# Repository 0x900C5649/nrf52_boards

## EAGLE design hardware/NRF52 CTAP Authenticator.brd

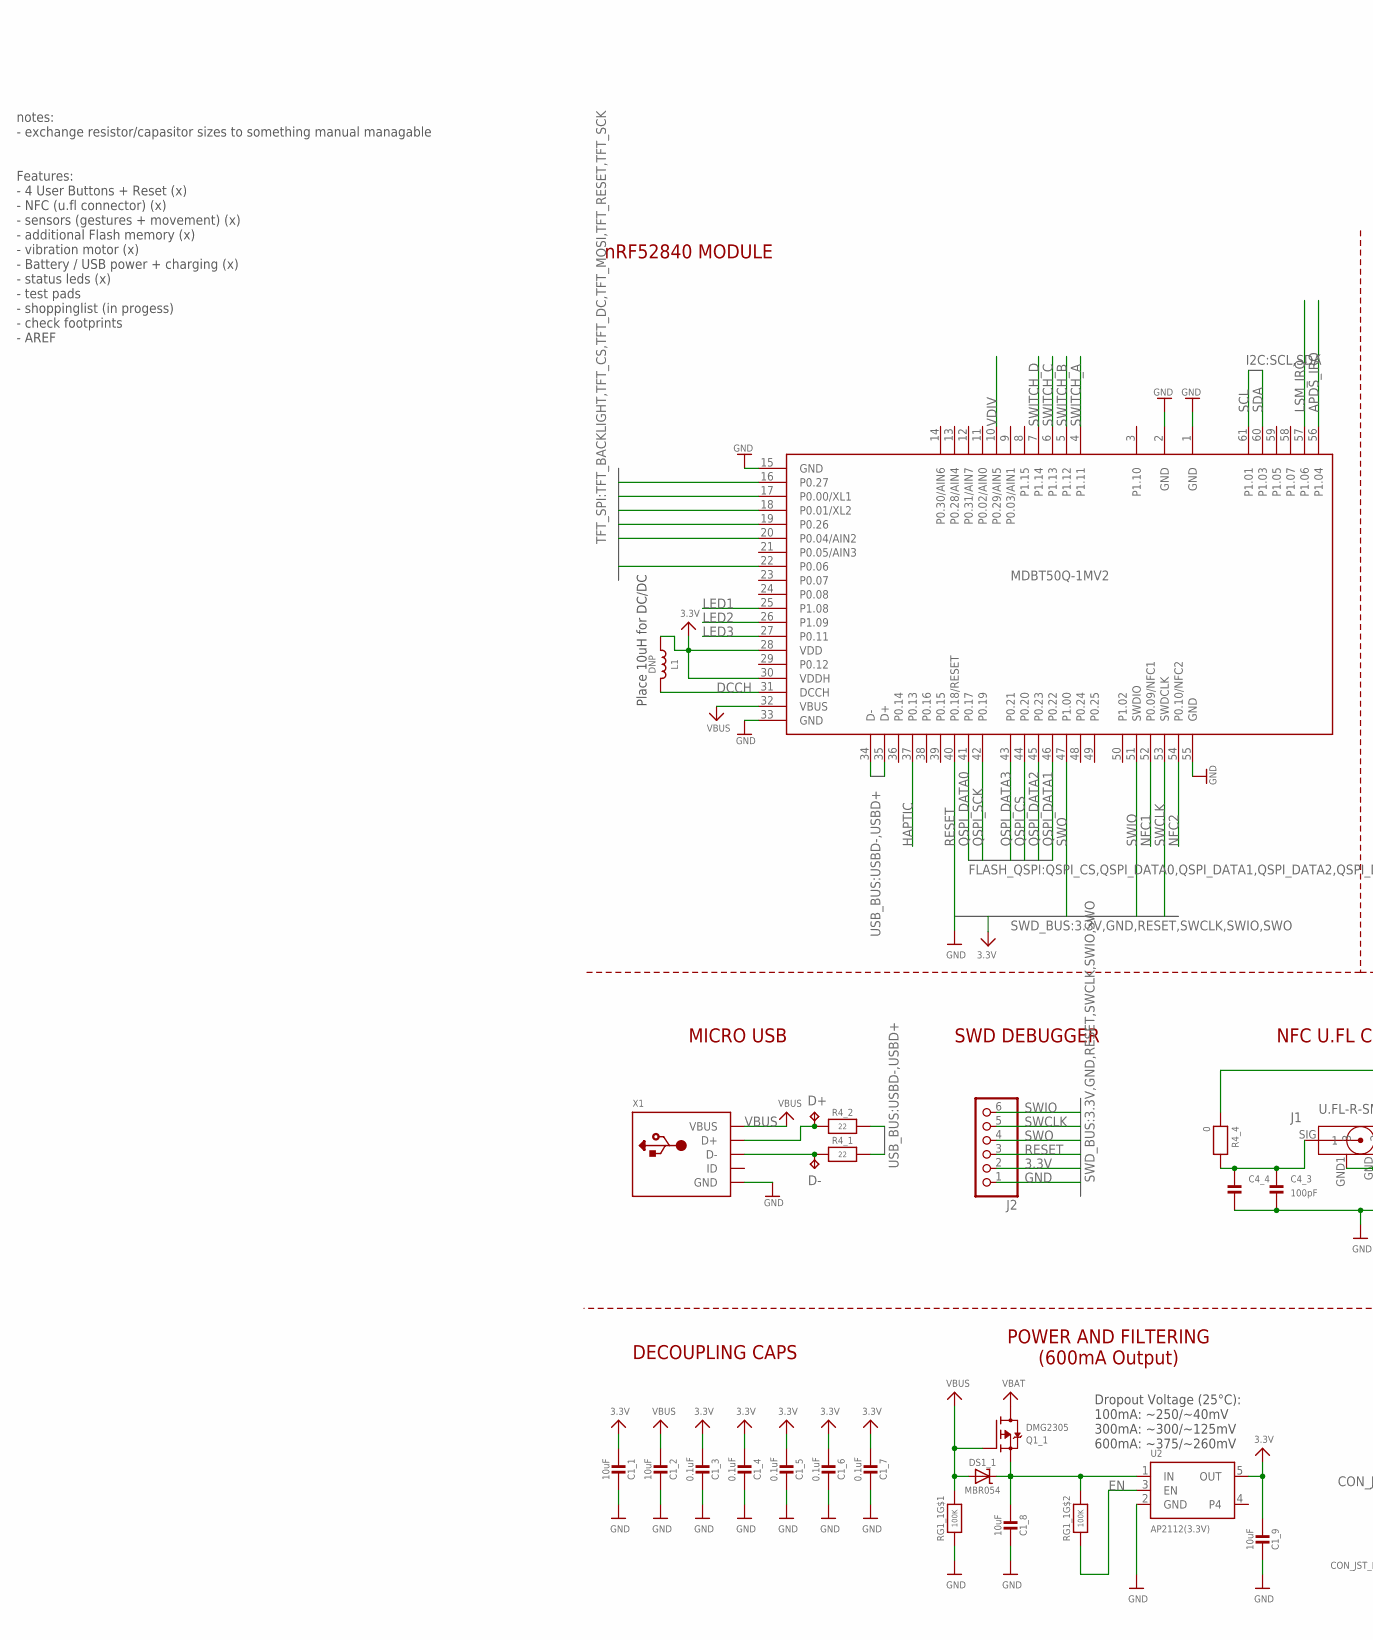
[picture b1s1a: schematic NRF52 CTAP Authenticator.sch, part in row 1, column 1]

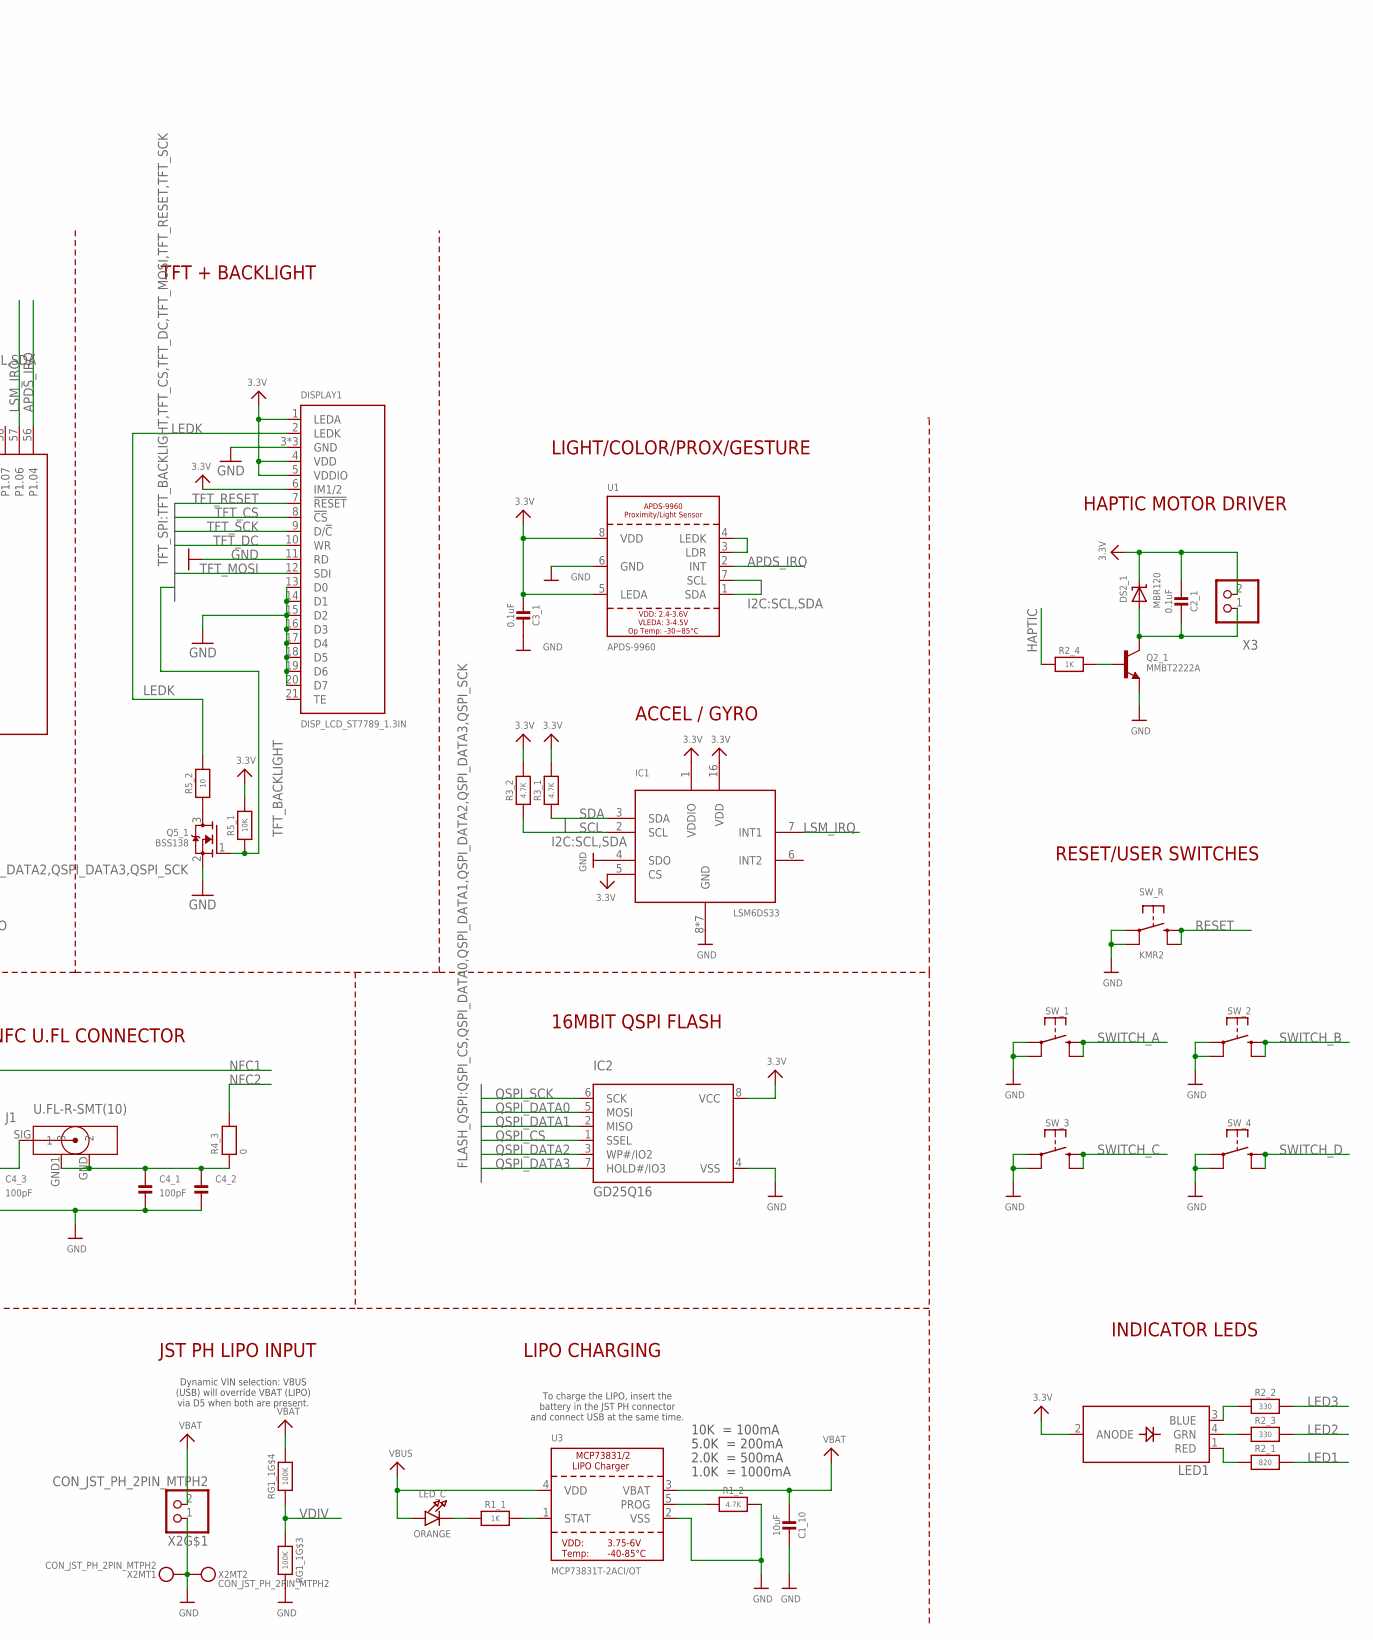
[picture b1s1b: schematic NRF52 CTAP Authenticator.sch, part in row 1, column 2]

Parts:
C1_1, C1_2, C1_8, C1_9, C1_10: 10uF; 0805_NOTHERMALS
C1_3, C1_4, C1_5, C1_6, C1_7, C2_1, C3_1: 0.1uF; 0805_NOTHERMALS
C4_1, C4_3: 100pF; 0805_NOTHERMALS
C4_2, C4_4: CAP_CERAMIC0805-NOTHERMALS; 0805_NOTHERMALS
D+: TPTP10R; TP10R
D-: TPTP10R; TP10R
DISPLAY1: DISP_LCD_ST7789_1.3IN; TFT_1.3IN_240X240_24P
DS1_1: MBR054; SOD-123
DS2_1: MBR120; SOD-123
IC1: LSM6DS33; LGA16_3X3MM
IC2: GD25Q16; SOIC8_150MIL
J1: U.FL-R-SMT(10)
J2: HEADER-1X6ROUND; 1X06_ROUND
L1: DNP; _0805MP
LED1: LED_RGB_PLCC4; RGBLED_PLCC4
LED_C: ORANGE; CHIPLED_0805_NOOUTLINE
MDBT50Q-1MV2: MDBT50
Q1_1: DMG2305; SOT23-R@1
Q2_1: MMBT2222A; SOT23-R
Q5_1: BSS138; SOT23-WIDE
R1_1, R2_4: 1K; 0805_NOTHERMALS
R1_2, R3_1, R3_2: 4.7K; 0805_NOTHERMALS
R2_1: 820; 0805_NOTHERMALS
R2_2, R2_3: 330; 0805_NOTHERMALS
R4_1, R4_2: 22; 0805_NOTHERMALS
R4_3, R4_4: 0; 0805_NOTHERMALS
R5_1: 10K; 0805_NOTHERMALS
R5_2: 10; 0805_NOTHERMALS
RG1_1: 100K; RESPACK_4X0603
SW_1, SW_2, SW_3, SW_4: SWITCH_TACT_SMT_6MM; 6MMX6MM_TACTILE_SMT
SW_R: KMR2; BTN_KMR2_4.6X2.8
U1: APDS-9960
U2: AP2112(3.3V); SOT23-5
U3: MCP73831T-2ACI/OT; SOT23-5
X1: USB_MICRO_20329_V2; 4UCONN_20329_V2
X2: CON_JST_PH_2PIN_MTPH2; JSTPH2
X3: CON_JST_PH_2PINPH2_NOTHERMALS; JSTPH2_NOTHERMALS

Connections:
3.3V: C1_1.2, C1_3.2, C1_4.2, C1_5.2, C1_6.2, C1_7.2, C1_9.2, C2_1.2, C3_1.2, DISPLAY1.1 (LEDA), DISPLAY1.4 (VDD), DISPLAY1.5 (VDDIO), DISPLAY1.6 (IM1/2), DS2_1.C, IC1.1 (VDDIO), IC1.5 (CS), IC1.16 (VDD), IC2.8 (VCC), J2.2, L1.1, LED1.2 (ANODE), MDBT50Q-1MV2.28 (VDD), MDBT50Q-1MV2.30 (VDDH), R3_1.2, R3_2.2, R5_1.2, U1.5 (LEDA), U1.8 (VDD), U2.5 (OUT), X3.2
APDS_IRQ: MDBT50Q-1MV2.56 (P1.04), U1.2 (INT)
D+: D+.TP, R4_2.1, X1.D+
D-: D-.TP, R4_1.1, X1.D-
DCCH: L1.2, MDBT50Q-1MV2.31 (DCCH)
EN: RG1_1.2 (1), U2.3 (EN)
GND: C1_1.1, C1_2.1, C1_3.1, C1_4.1, C1_5.1, C1_6.1, C1_7.1, C1_8.1, C1_9.1, C1_10.1, C3_1.1, C4_1.2, C4_2.2, C4_3.2, C4_4.2, DISPLAY1.3 (GND), DISPLAY1.11 (RD), DISPLAY1.13 (D0), DISPLAY1.14 (D1), DISPLAY1.15 (D2), DISPLAY1.16 (D3), DISPLAY1.17 (D4), DISPLAY1.18 (D5), DISPLAY1.19 (D6), DISPLAY1.20 (D7), DISPLAY1.23 (GND), DISPLAY1.24 (GND), IC1.4 (SDO), IC1.8 (GND), IC1.9 (GND), IC1.10 (GND), IC1.11 (GND), IC1.12 (GND), IC1.13 (GND), IC1.15 (GND), IC2.4 (VSS), J2.1, MDBT50Q-1MV2.1 (GND), MDBT50Q-1MV2.2 (GND), MDBT50Q-1MV2.15 (GND), MDBT50Q-1MV2.33 (GND), MDBT50Q-1MV2.55 (GND), Q2_1.2 (E), Q5_1.2 (S), R1_2.2, RG1_1.1, RG1_1.6 (2), SW_1.A, SW_1.A' (P1), SW_2.A, SW_2.A' (P1), SW_3.A, SW_3.A' (P1), SW_4.A, SW_4.A' (P1), SW_R.A, SW_R.A' (P1), U1.6 (GND), U2.2 (GND), U3.2 (VSS), X1.BASE@1 (GND), X1.BASE@2 (GND), X1.GND, X1.SPRT@1 (GND), X1.SPRT@2 (GND), X1.SPRT@3 (GND), X1.SPRT@4 (GND), X2.1, X2.NC1, X2.NC2
HAPTIC: MDBT50Q-1MV2.37 (P0.13), R2_4.1
LED1: MDBT50Q-1MV2.25 (P1.08), R2_1.2
LED2: MDBT50Q-1MV2.26 (P1.09), R2_3.2
LED3: MDBT50Q-1MV2.27 (P0.11), R2_2.2
LEDK: DISPLAY1.2 (LEDK), R5_2.2
LSM_IRQ: IC1.7 (INT1), MDBT50Q-1MV2.57 (P1.06)
unnamed: LED_C.C, R1_1.1
unnamed: U1.3 (LDR), U1.4 (LEDK)
unnamed: LED1.3 (BLUE), R2_2.1
unnamed: Q5_1.3 (D), R5_2.1
unnamed: LED1.4 (GRN), R2_3.1
unnamed: C4_1.1, C4_2.1, J1.GND (2), J1.GND1 (3), R4_3.1
unnamed: C2_1.1, DS2_1.A, Q2_1.3 (C), X3.1
unnamed: C4_3.1, C4_4.1, J1.SIG (1), R4_4.2
unnamed: Q2_1.1 (B), R2_4.2
unnamed: LED1.1 (RED), R2_1.1
unnamed: R1_1.2, U3.1 (STAT)
unnamed: R1_2.1, U3.5 (PROG)
NFC1: MDBT50Q-1MV2.52 (P0.09/NFC1), R4_4.1
NFC2: MDBT50Q-1MV2.54 (P0.10/NFC2), R4_3.2
QSPI_CS: IC2.1 (SSEL), MDBT50Q-1MV2.44 (P0.20)
QSPI_DATA0: IC2.5 (MOSI), MDBT50Q-1MV2.41 (P0.17)
QSPI_DATA1: IC2.2 (MISO), MDBT50Q-1MV2.46 (P0.22)
QSPI_DATA2: IC2.3 (WP#/IO2), MDBT50Q-1MV2.45 (P0.23)
QSPI_DATA3: IC2.7 (HOLD#/IO3), MDBT50Q-1MV2.43 (P0.21)
QSPI_SCK: IC2.6 (SCK), MDBT50Q-1MV2.42 (P0.19)
RESET: J2.3, MDBT50Q-1MV2.40 (P0.18/RESET), SW_R.B (S), SW_R.B' (S1)
SCL: IC1.2 (SCL), MDBT50Q-1MV2.61 (P1.01), R3_2.1, U1.7 (SCL)
SDA: IC1.3 (SDA), MDBT50Q-1MV2.60 (P1.03), R3_1.1, U1.1 (SDA)
SWCLK: J2.5, MDBT50Q-1MV2.53 (SWDCLK)
SWIO: J2.6, MDBT50Q-1MV2.51 (SWDIO)
SWITCH_A: MDBT50Q-1MV2.4 (P1.11), SW_1.B (S), SW_1.B' (S1)
SWITCH_B: MDBT50Q-1MV2.5 (P1.12), SW_2.B (S), SW_2.B' (S1)
SWITCH_C: MDBT50Q-1MV2.6 (P1.13), SW_3.B (S), SW_3.B' (S1)
SWITCH_D: MDBT50Q-1MV2.7 (P1.14), SW_4.B (S), SW_4.B' (S1)
SWO: J2.4, MDBT50Q-1MV2.47 (P1.00)
TFT_BACKLIGHT: MDBT50Q-1MV2.16 (P0.27), Q5_1.1 (G), R5_1.1
TFT_CS: DISPLAY1.8 (!CS), MDBT50Q-1MV2.18 (P0.01/XL2)
TFT_DC: DISPLAY1.10 (WR), MDBT50Q-1MV2.20 (P0.04/AIN2)
TFT_MOSI: DISPLAY1.12 (SDI), MDBT50Q-1MV2.22 (P0.06)
TFT_RESET: DISPLAY1.7 (!RESET), MDBT50Q-1MV2.17 (P0.00/XL1)
TFT_SCK: DISPLAY1.9 (D/!C), MDBT50Q-1MV2.19 (P0.26)
USBD+: MDBT50Q-1MV2.35 (D+), R4_2.2
USBD-: MDBT50Q-1MV2.34 (D-), R4_1.2
VBAT: C1_10.2, Q1_1.3 (D), RG1_1.5 (2), U3.3 (VBAT), X2.2
VBUS: C1_2.2, DS1_1.A, LED_C.A, MDBT50Q-1MV2.32 (VBUS), Q1_1.1 (G), RG1_1.8 (2), U3.4 (VDD), X1.VBUS
VDIV: MDBT50Q-1MV2.10 (P0.29/AIN5), RG1_1.3 (1), RG1_1.4 (1)
VHI: C1_8.2, DS1_1.C, Q1_1.2 (S), RG1_1.7 (2), U2.1 (IN)

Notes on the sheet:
10K = 100mA
5.0K = 200mA
2.0K = 500mA
1.0K = 1000mA
LIPO CHARGING
To charge the LIPO, insert the battery in the JST PH connector and connect USB at the same time.
POWER AND FILTERING (600mA Output)
JST PH LIPO INPUT
Dynamic VIN selection: VBUS (USB) will override VBAT (LIPO) via D5 when both are present.
Dropout Voltage (25°C): 100mA: ~250/~40mV 300mA: ~300/~125mV 600mA: ~375/~260mV
INDICATOR LEDS
16MBIT QSPI FLASH
MICRO USB
ACCEL / GYRO
LIGHT/COLOR/PROX/GESTURE
RESET/USER SWITCHES
TFT + BACKLIGHT
SWD DEBUGGER
Place 10uH for DC/DC
DECOUPLING CAPS
notes: - exchange resistor/capasitor sizes to something manual managable Features: - 4 User Buttons + Reset (x) - NFC (u.fl connector) (x) - sensors (gestures + movement) (x) - additional Flash memory (x) - vibration motor (x) - Battery / USB power + charging (x) - status leds (x) - test pads - sho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
NFC U.FL CONNECTOR
nRF52840 MODULE
HAPTIC MOTOR DRIVER

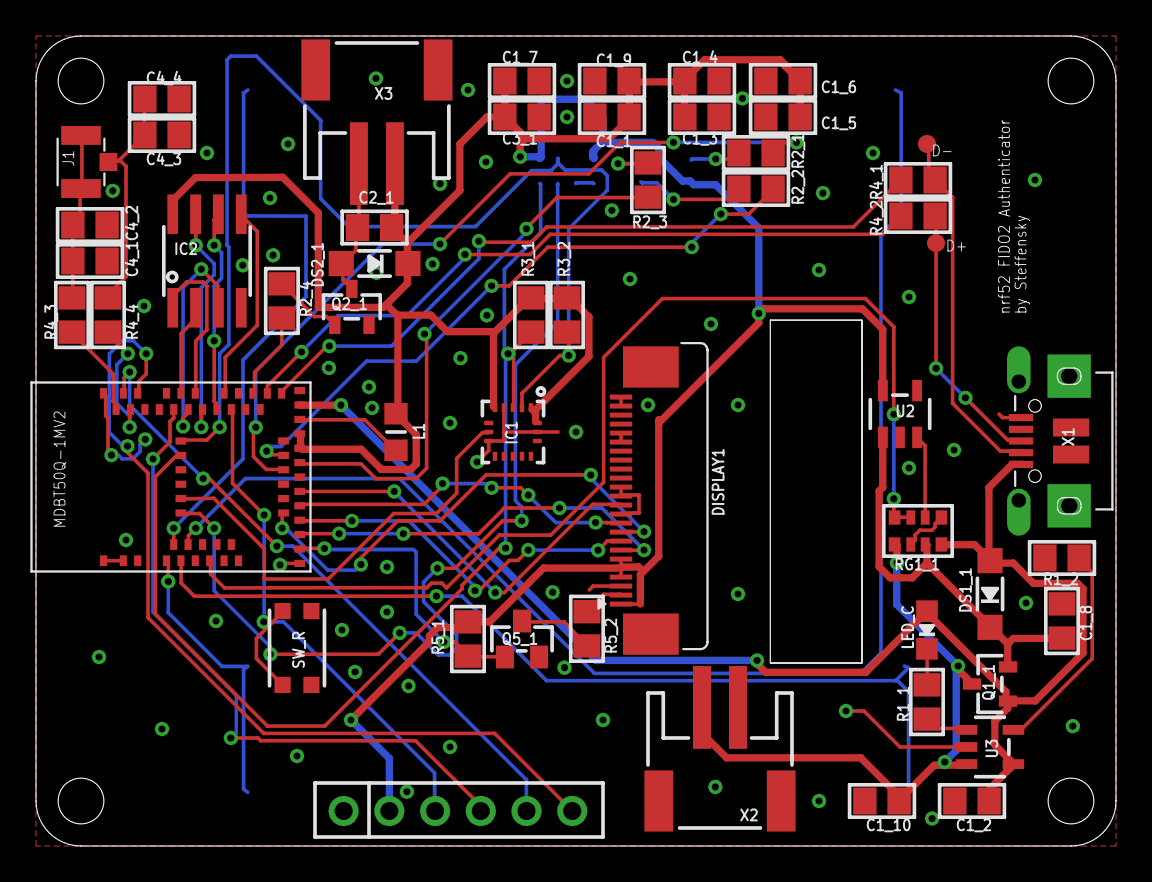
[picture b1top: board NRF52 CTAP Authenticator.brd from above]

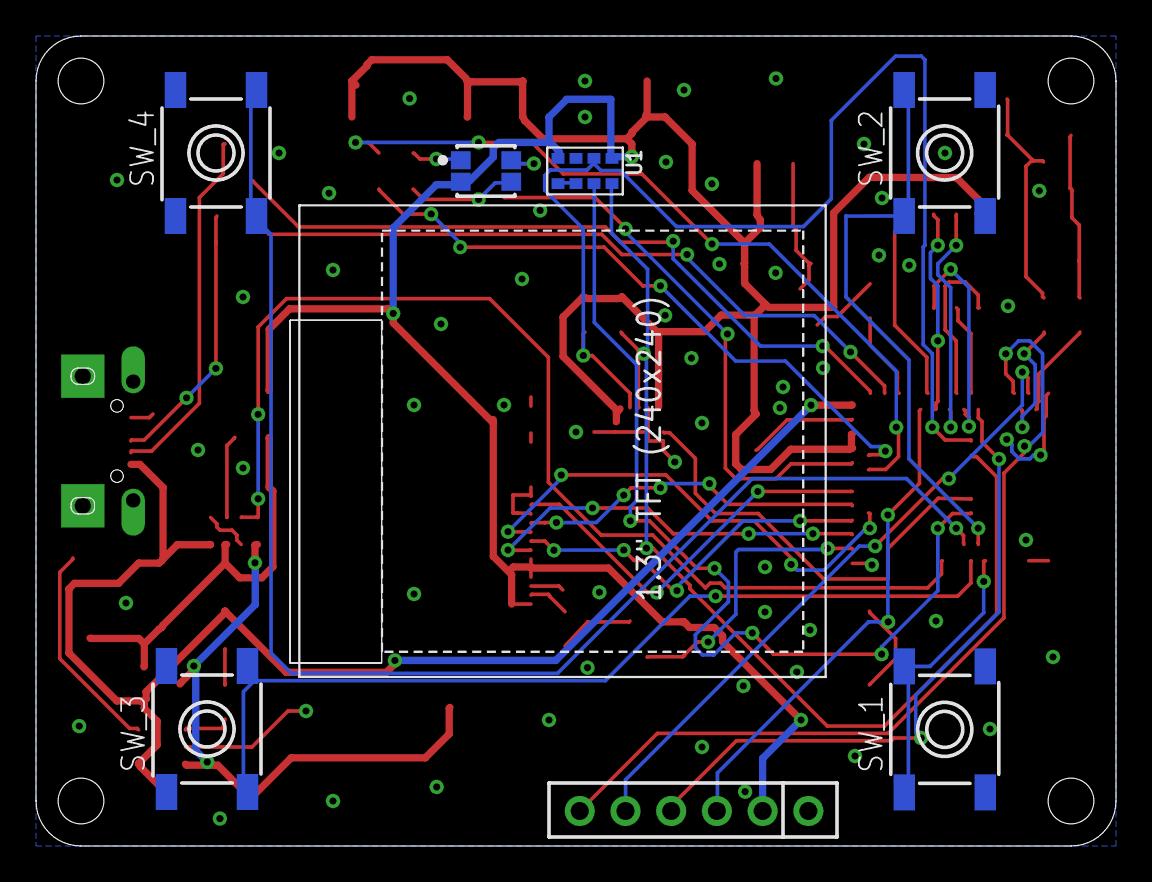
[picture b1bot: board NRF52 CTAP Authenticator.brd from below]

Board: 2 copper layers, 60.0 x 45.0 mm, 58 parts (6 on the bottom side), 55 nets.

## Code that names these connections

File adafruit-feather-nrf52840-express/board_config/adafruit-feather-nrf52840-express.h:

/**
 * Copyright (c) 2016 - 2018, Nordic Semiconductor ASA
 * 
 * All rights reserved.
 * 
 * Redistribution and use in source and binary forms, with or without modification,
 * are permitted provided that the following conditions are met:
 * 
 * 1. Redistributions of source code must retain the above copyright notice, this
 *    list of conditions and the following disclaimer.
 * 
 * 2. Redistributions in binary form, except as embedded into a Nordic
 *    Semiconductor ASA integrated circuit in a product or a software update for
 *    such product, must reproduce the above copyright notice, this list of
 *    conditions and the following disclaimer in the documentation and/or other
 *    materials provided with the distribution.
 * 
 * 3. Neither the name of Nordic Semiconductor ASA nor the names of its
 *    contributors may be used to endorse or promote products derived from this
 *    software without specific prior written permission.
 * 
 * 4. This software, with or without modification, must only be used with a
 *    Nordic Semiconductor ASA integrated circuit.
 * 
 * 5. Any software provided in binary form under this license must not be reverse
 *    engineered, decompiled, modified and/or disassembled.
 * 
 * THIS SOFTWARE IS PROVIDED BY NORDIC SEMICONDUCTOR ASA "AS IS" AND ANY EXPRESS
 * OR IMPLIED WARRANTIES, INCLUDING, BUT NOT LIMITED TO, THE IMPLIED WARRANTIES
 * OF MERCHANTABILITY, NONINFRINGEMENT, AND FITNESS FOR A PARTICULAR PURPOSE ARE
 * DISCLAIMED. IN NO EVENT SHALL NORDIC SEMICONDUCTOR ASA OR CONTRIBUTORS BE
 * LIABLE FOR ANY DIRECT, INDIRECT, INCIDENTAL, SPECIAL, EXEMPLARY, OR
 * CONSEQUENTIAL DAMAGES (INCLUDING, BUT NOT LIMITED TO, PROCUREMENT OF SUBSTITUTE
 * GOODS OR SERVICES; LOSS OF USE, DATA, OR PROFITS; OR BUSINESS INTERRUPTION)
 * HOWEVER CAUSED AND ON ANY THEORY OF LIABILITY, WHETHER IN CONTRACT, STRICT
 * LIABILITY, OR TORT (INCLUDING NEGLIGENCE OR OTHERWISE) ARISING IN ANY WAY OUT
 * OF THE USE OF THIS SOFTWARE, EVEN IF ADVISED OF THE POSSIBILITY OF SUCH DAMAGE.
 * 
 */
#ifndef CUSTOM_BOARD_H
#define CUSTOM_BOARD_H

#ifdef __cplusplus
extern "C"
{
#endif

#include "nrf_gpio.h"

#define A0      NRF_GPIO_PIN_MAP(0, 4)
#define A1      NRF_GPIO_PIN_MAP(0, 5)
#define A2      NRF_GPIO_PIN_MAP(0, 30)
#define A3      NRF_GPIO_PIN_MAP(0, 28)
#define A4      NRF_GPIO_PIN_MAP(0, 2)
#define A5      NRF_GPIO_PIN_MAP(0, 3)

#define D2      NRF_GPIO_PIN_MAP(0, 10)
#define NC      D2
#define D5      NRF_GPIO_PIN_MAP(1, 8)
#define D6      NRF_GPIO_PIN_MAP(0, 7)
#define D9      NRF_GPIO_PIN_MAP(0, 26)
#define D10     NRF_GPIO_PIN_MAP(0, 27)
#define D11     NRF_GPIO_PIN_MAP(0, 6)
#define D12     NRF_GPIO_PIN_MAP(0, 8)
#define D13     NRF_GPIO_PIN_MAP(1, 9)

#define SDA     NRF_GPIO_PIN_MAP(0, 22)
#define SCL     NRF_GPIO_PIN_MAP(0, 22)

#define TX      NRF_GPIO_PIN_MAP(0, 11)
#define RX      NRF_GPIO_PIN_MAP(0, 12)

#define MISO    NRF_GPIO_PIN_MAP(0, 15)
#define MOSI    NRF_GPIO_PIN_MAP(0, 13)
#define SCK     NRF_GPIO_PIN_MAP(0, 14)

#define NEOPIX      NRF_GPIO_PIN_MAP(0, 16)

#define QSPI_SCK    NRF_GPIO_PIN_MAP(0, 19)
#define QSPI_DATA0  NRF_GPIO_PIN_MAP(0, 17)
#define QSPI_DATA1  NRF_GPIO_PIN_MAP(0, 22)
#define QSPI_CS     NRF_GPIO_PIN_MAP(0, 20)
#define QSPI_DATA2  NRF_GPIO_PIN_MAP(0, 23)
#define QSPI_DATA3  NRF_GPIO_PIN_MAP(0, 21)

#define SWO         NRF_GPIO_PIN_MAP(1, 0)

#define SWITCH      NRF_GPIO_PIN_MAP(1, 2)


// LEDs definitions for nRF52840-MDK
#define LEDS_NUMBER 2

#define LED_START LED_1
#define LED_1     NRF_GPIO_PIN_MAP(1, 15)
#define LED_RED   LED1
#define LED_2     NRF_GPIO_PIN_MAP(1, 10)
#define LED_BLUE  LED_2
#define LED_STOP  LED_2

#define LEDS_ACTIVE_STATE 1
#define LEDS_ACTIVE_HIGH true

#define LEDS_LIST           \
    {                       \
        LED_1, LED_2        \
    }

#define LEDS_INV_MASK 0

#define BSP_LED_0 LED_1
#define BSP_LED_1 LED_2


#define BUTTONS_NUMBER 1

#define BUTTON_0    SWITCH
#define BUTTON_PULL NRF_GPIO_PIN_PULLUP

#define BUTTONS_ACTIVE_STATE 0

#define BUTTONS_LIST \
    {                \
        BUTTON_0     \
    }

#define BSP_BUTTON_0 BUTTON_0


#define BTN_USER 0

//#define CTS_PIN_NUMBER 7
//#define RTS_PIN_NUMBER 5
#define HWFC           false

#define BSP_QSPI_SCK_PIN    QSPI_SCK
#define BSP_QSPI_CSN_PIN    QSPI_CS
#define BSP_QSPI_IO0_PIN    QSPI_DATA0
#define BSP_QSPI_IO1_PIN    QSPI_DATA1
#define BSP_QSPI_IO2_PIN    QSPI_DATA2
#define BSP_QSPI_IO3_PIN    QSPI_DATA3


#ifdef USE_APP_BOARDCONFIG
#include STRINGIFY(BOARD/app_board_config.h)
#endif

#ifdef __cplusplus
}
#endif

#endif  // CUSTOM_BOARD_H

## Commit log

2020-02-19 moving to own repo
2020-03-05 hid wip
2020-03-17 first test running
2020-03-17 cleanup tinycbor
2020-04-07 working fds
2020-04-28 usb kinda working
2020-06-15 branch init: wip
2020-06-16 ble working
2020-06-23 (wip) nfc implementation
2020-06-25 nfc wip + clang-format
2020-07-30 nfc status update
2020-07-30 nfc test jupyter noteboot
2020-07-30 hardware rev A
2020-08-04 nfc u2f working with android
2020-08-11 init repo
2020-08-11 adafruit feather nrf52840 + makerdiary nrf52840 usb dongle
2020-08-11 make file
2020-08-11 make files
2020-08-11 tiny changes
2020-08-11 update makefile
2020-08-11 boards update
2020-08-12 nfc update
2020-08-17 hardware revison 2
2020-08-24 eagle gitignore
2020-09-01 nfc test update
2020-09-07 move boards
2020-09-07 new boards
2020-09-07 board configs
2020-09-07 USE_APP_BOARDCONFIG
2020-09-07 rm log.log
2020-09-07 enable setting dirs
2020-09-07 rename board config
2020-09-07 macro name
2020-09-07 custom board inc
2020-09-07 always include incl_dir
2020-09-07 feather nrf52840 minor fix
2020-09-08 moved BOARD string configuration
2020-09-08 led fixes to adafruit feather nrf52840 express
2020-09-17 feat: add authWG M1 board

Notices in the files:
parts and their libraries:
microbuilder: This work is placed in the public domain, and may be freely used for commercial and non-commercial work with the following conditions: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
